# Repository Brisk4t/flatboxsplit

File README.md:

# FlatboxSplit: Hitbox-Layout fightstick with Gateron low profile switches
Original Design inspired by [Flatbox by JFedor](https://github.com/jfedor2/flatbox).

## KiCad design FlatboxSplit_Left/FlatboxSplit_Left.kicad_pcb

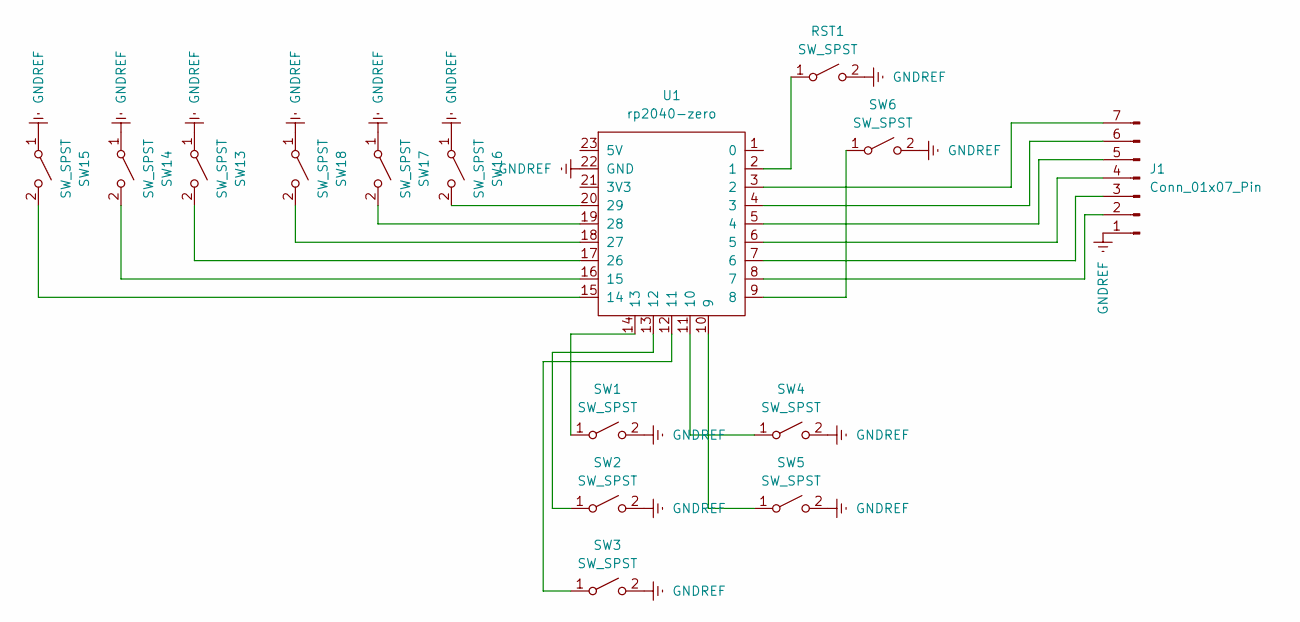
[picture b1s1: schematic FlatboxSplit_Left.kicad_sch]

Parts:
J1: Conn_01x07_Pin; PinHeader_1x07_P2.54mm_Vertical
RST1: SW_SPST; SW_PUSH_6mm
SW1, SW2, SW3, SW4, SW5, SW6: SW_SPST; gateron-ks27
SW13, SW14, SW15, SW16, SW17, SW18: SW_SPST; SW_PUSH_6mm
U1: rp2040-zero; rp2040-zero-tht

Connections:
GNDREF: J1.1, RST1.2 (B), SW1.2 (B), SW2.2 (B), SW3.2 (B), SW4.2 (B), SW5.2 (B), SW6.2 (B), SW13.1 (A), SW14.1 (A), SW15.1 (A), SW16.1 (A), SW17.1 (A), SW18.1 (A), U1.22 (GND)
unnamed: J1.2, U1.8 (7)
unnamed: J1.3, U1.7 (6)
unnamed: J1.4, U1.6 (5)
unnamed: J1.5, U1.5 (4)
unnamed: J1.6, U1.4 (3)
unnamed: J1.7, U1.3 (2)
unnamed: RST1.1 (A), U1.2 (1)
unnamed: SW1.1 (A), U1.14 (13)
unnamed: SW2.1 (A), U1.13 (12)
unnamed: SW3.1 (A), U1.12 (11)
unnamed: SW4.1 (A), U1.11 (10)
unnamed: SW5.1 (A), U1.10 (9)
unnamed: SW6.1 (A), U1.9 (8)
unnamed: SW13.2 (B), U1.17 (26)
unnamed: SW14.2 (B), U1.16 (15)
unnamed: SW15.2 (B), U1.15 (14)
unnamed: SW16.2 (B), U1.20 (29)
unnamed: SW17.2 (B), U1.19 (28)
unnamed: SW18.2 (B), U1.18 (27)

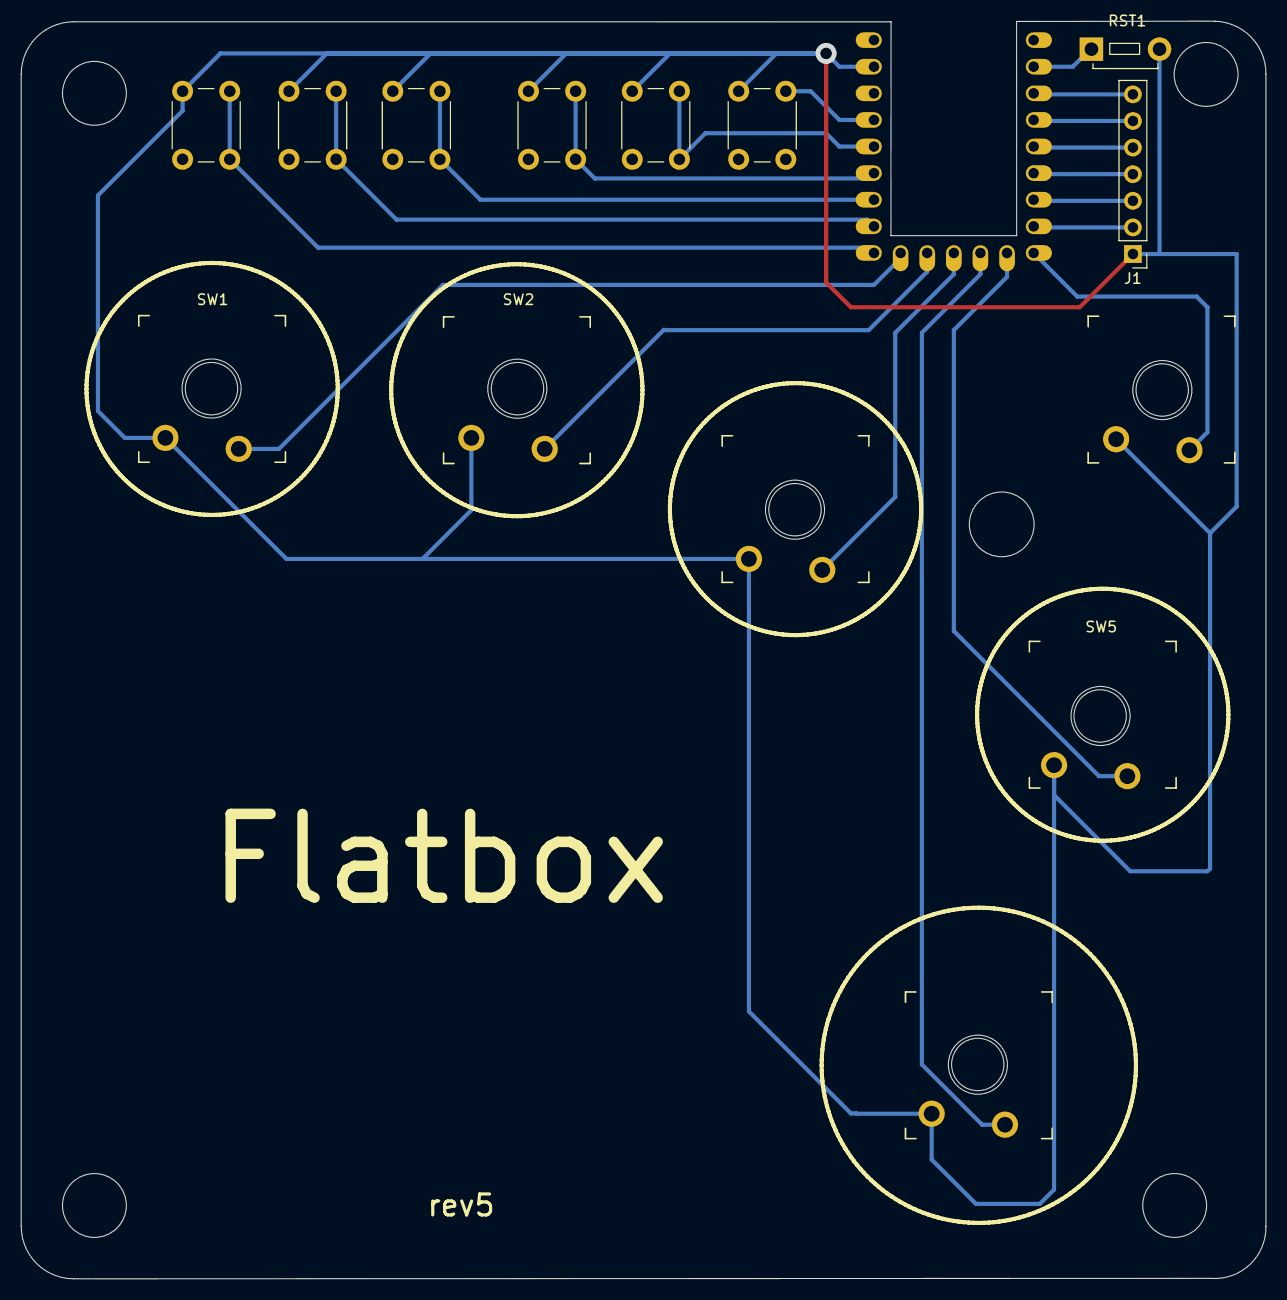
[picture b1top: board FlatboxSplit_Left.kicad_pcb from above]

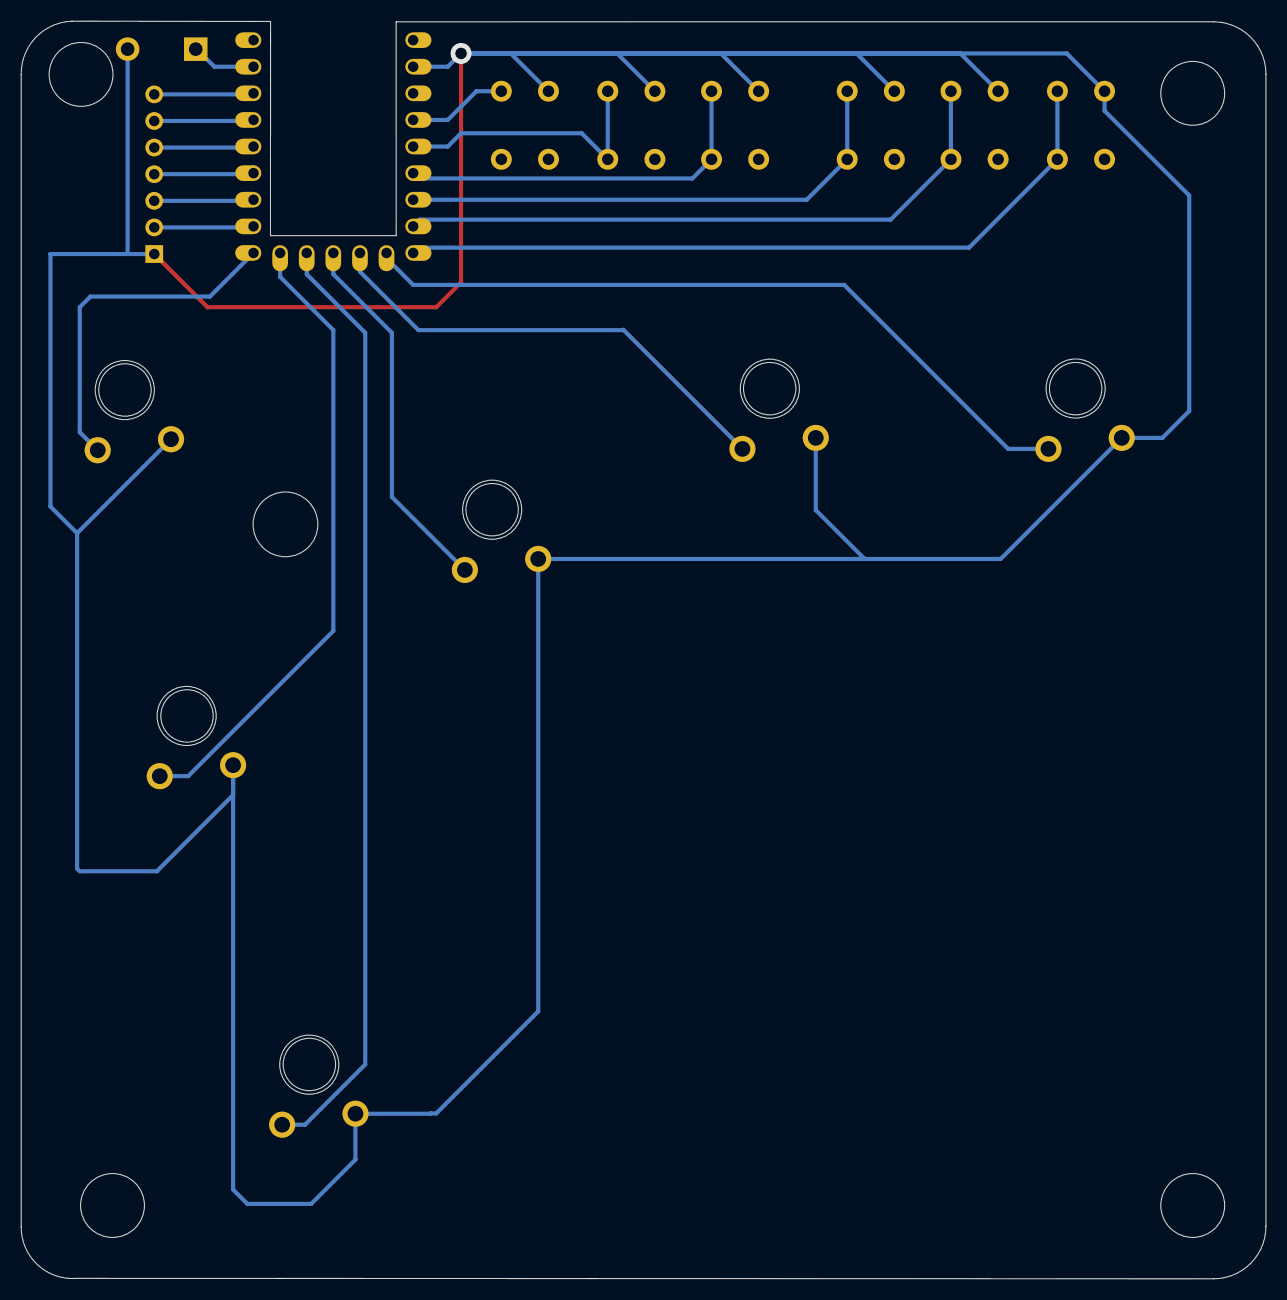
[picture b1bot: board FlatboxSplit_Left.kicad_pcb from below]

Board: 2 copper layers, 118.8 x 120.1 mm, 15 parts (14 on the bottom side), 20 nets.

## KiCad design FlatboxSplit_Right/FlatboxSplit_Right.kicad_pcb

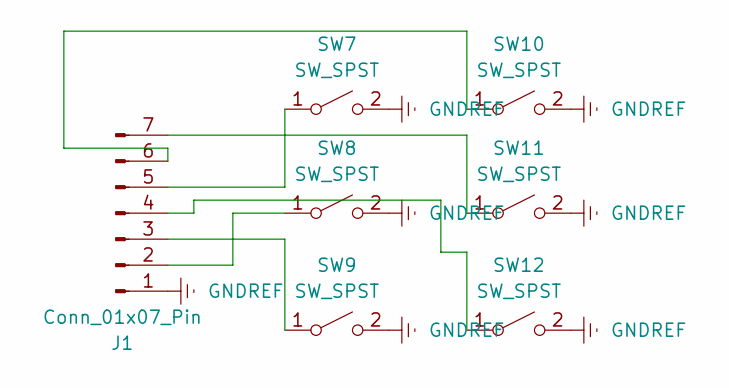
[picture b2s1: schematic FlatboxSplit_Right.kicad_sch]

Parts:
J1: Conn_01x07_Pin; PinHeader_1x07_P2.54mm_Vertical
SW7, SW8, SW9, SW10, SW11, SW12: SW_SPST; gateron-ks27

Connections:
GNDREF: J1.1, SW7.2 (B), SW8.2 (B), SW9.2 (B), SW10.2 (B), SW11.2 (B), SW12.2 (B)
unnamed: J1.2, SW8.1 (A)
unnamed: J1.3, SW9.1 (A)
unnamed: J1.4, SW12.1 (A)
unnamed: J1.5, SW7.1 (A)
unnamed: J1.6, SW10.1 (A)
unnamed: J1.7, SW11.1 (A)

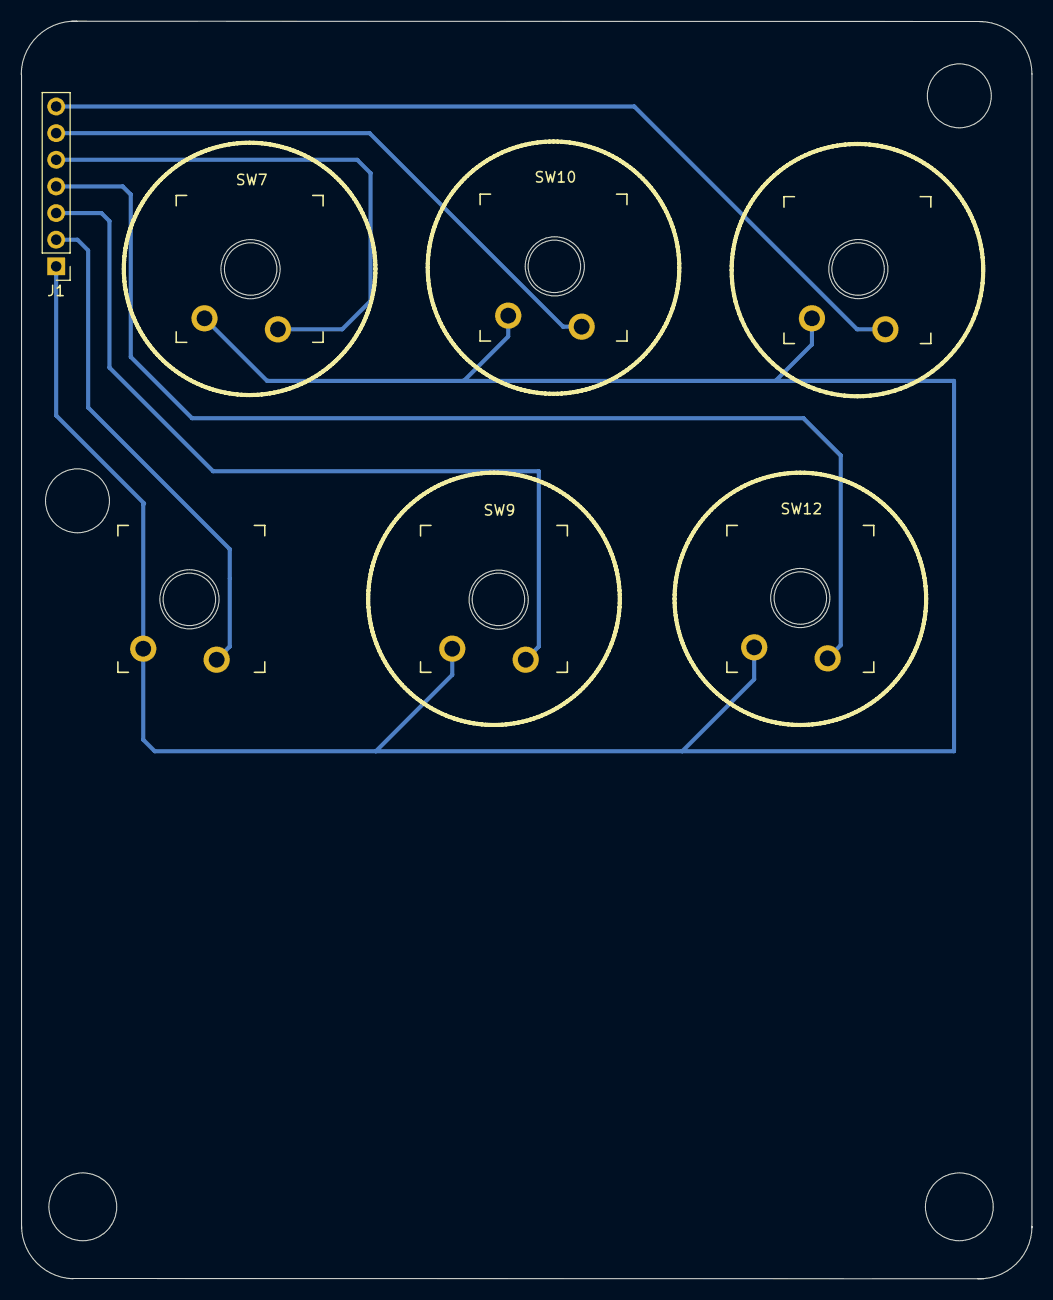
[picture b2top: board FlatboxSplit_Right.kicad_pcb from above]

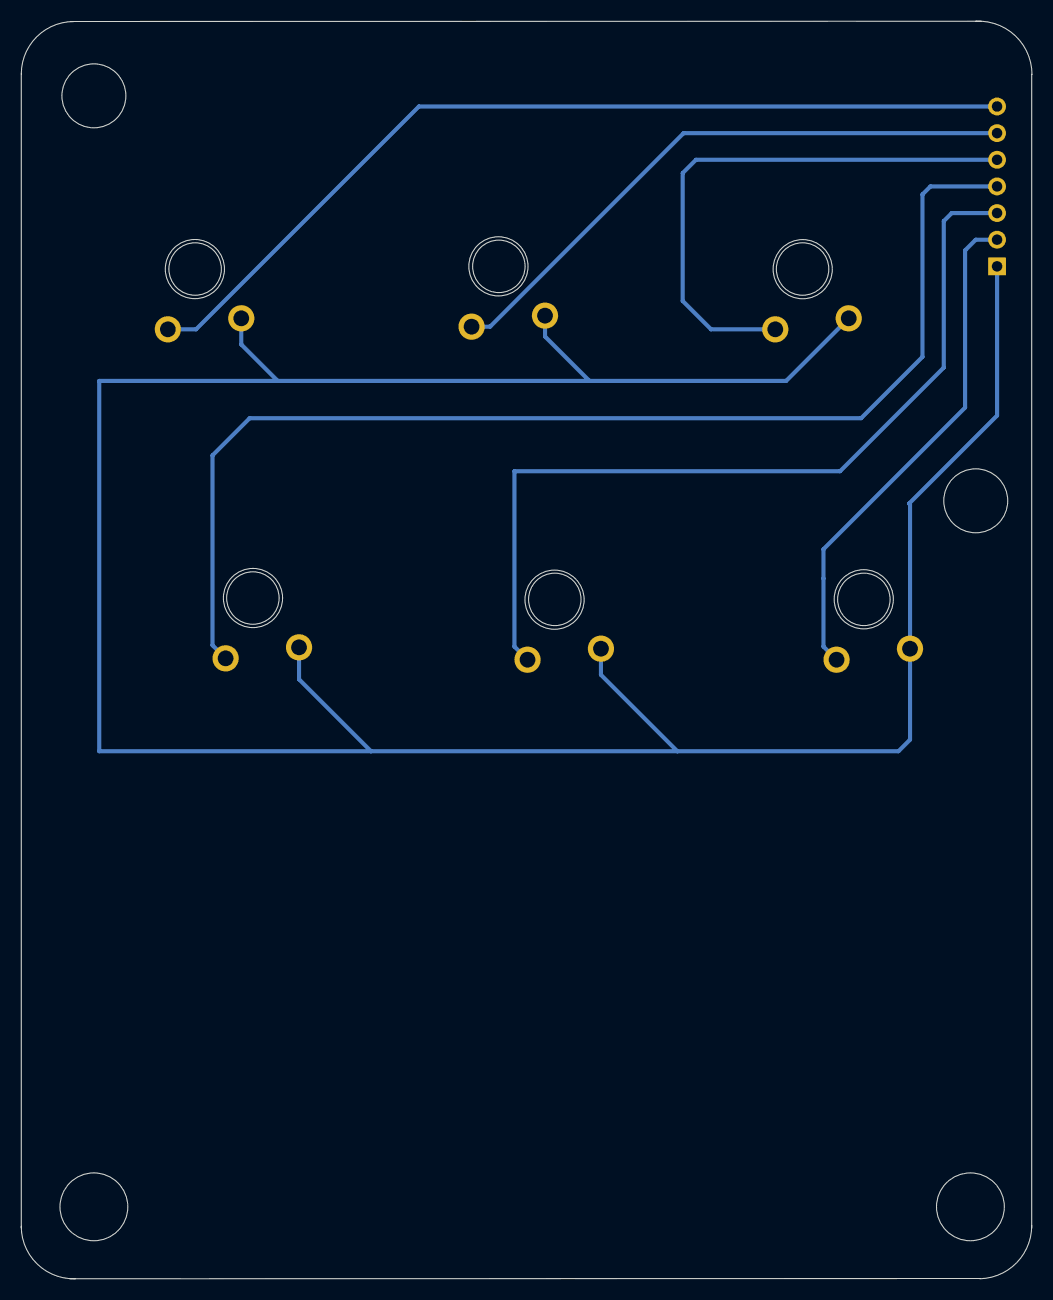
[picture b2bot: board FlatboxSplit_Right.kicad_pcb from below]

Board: 2 copper layers, 96.4 x 119.9 mm, 7 parts (7 on the bottom side), 7 nets.

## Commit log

2024-08-31 added pcb files
